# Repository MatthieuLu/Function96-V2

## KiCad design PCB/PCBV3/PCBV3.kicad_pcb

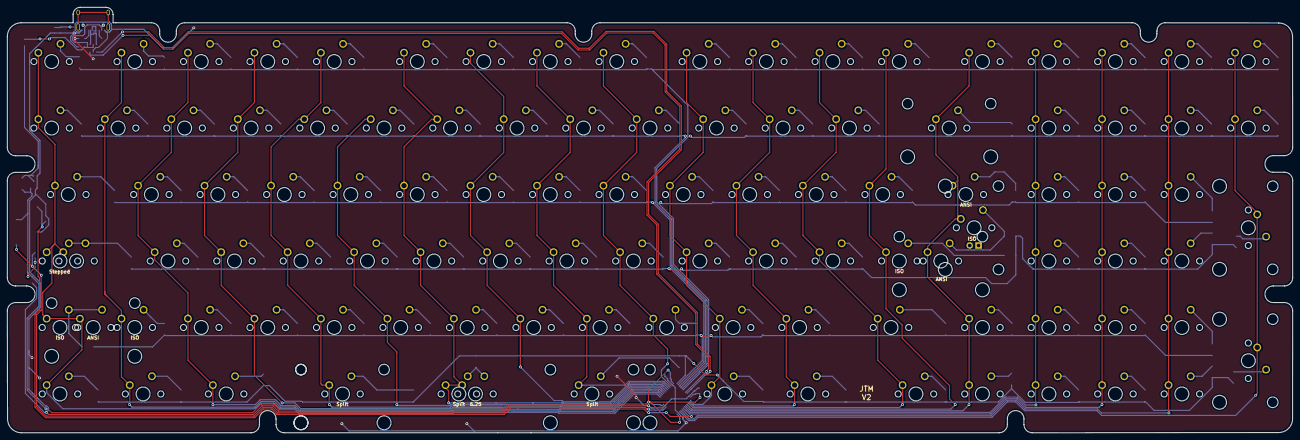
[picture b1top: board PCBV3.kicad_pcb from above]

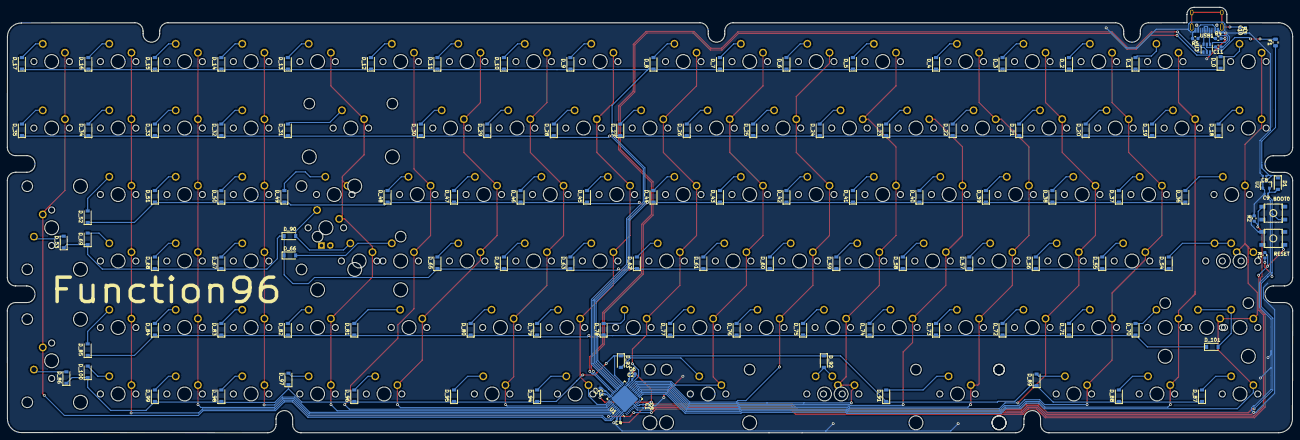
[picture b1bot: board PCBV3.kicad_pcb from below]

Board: 2 copper layers, 368.3 x 121.9 mm, 232 parts (126 on the bottom side), 140 nets.

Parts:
BOOT0: SW_PUSH; SKQG-1155865
C1: 10nF; C_0402_1005Metric
C2, C3, C4: 100nF; C_0402_1005Metric
C5: 1uF; C_0402_1005Metric
C6, C7: 4.7uF; C_0603_1608Metric
C8, C9: 0.1uF; C_0402_1005Metric
C10: 4.7nF; C_0603_1608Metric
C11: 100nF; C_0603_1608Metric
D1: D_Schottky; D_SOD-123
D_0, D_1, D_2, D_3, D_4, D_5, D_6, D_7, D_8, D_9, D_10, D_11, D_12, D_13, D_14, D_15, D_16, D_17, D_18, D_19, D_20, D_21, D_22, D_23, D_24, D_25, D_26, D_27, D_28, D_29, D_30, D_31, D_32, D_33, D_34, D_35, D_36, D_37, D_38, D_39, D_40, D_41, D_42, D_43, D_44, D_45, D_46, D_47, D_48, D_49, D_50, D_51, D_52, D_53, D_54, D_55, D_56, D_57, D_58, D_59, D_60, D_61, D_62, D_63, D_64, D_65, D_66, D_67, D_68, D_69, D_70, D_71, D_72, D_73, D_74, D_75, D_76, D_77, D_78, D_79, D_80, D_81, D_82, D_83, D_84, D_85, D_86, D_87, D_88, D_89, D_90, D_91, D_92, D_93, D_94, D_95, D_96, D_97, D_98, D_99, D_100, D_101: D; D_SOD-123
F1: Polyfuse_Small; Fuse_0805_2012Metric
K_0, K_1, K_2, K_3, K_4, K_5, K_6, K_7, K_8, K_9, K_10, K_11, K_12, K_13, K_14, K_15, K_16, K_17, K_18, K_19, K_20, K_21, K_22, K_23, K_24, K_25, K_26, K_27, K_28, K_29, K_30, K_32, K_33, K_34, K_35, K_37, K_38, K_39, K_40, K_41, K_42, K_43, K_44, K_45, K_46, K_47, K_48, K_50, K_51, K_52, K_55, K_56, K_57, K_58, K_59, K_60, K_61, K_62, K_63, K_64, K_65, K_67, K_68, K_69, K_71, K_72, K_73, K_74, K_75, K_76, K_77, K_78, K_79, K_80, K_82, K_83, K_84, K_85, K_96, K_97, K_98, K_99, K_100: KEYSW; MXOnly-1U-NoLED
K_31, K_53, K_86: KEYSW; MXOnly-2U-NoLED
K_36, K_49ANSISlash1: KEYSW; MXOnly-1.5U-NoLED
K_54, K_81: KEYSW; MXOnly-1.75U-NoLED
K_87, K_88, K_89, K_92, K_94, K_95, K_101: KEYSW; MXOnly-1.25U-NoLED
K_90: KEYSW; MXOnly-6.25U-NoLED
K_91: KEYSW; MXOnly-2.25U-NoLED
K_93: KEYSW; MXOnly-2.75U-NoLED
K_ANSIEnter1: KEYSW; MXOnly-2.25U-NoLED
K_ANSIShift1: KEYSW; MXOnly-2.25U-NoLED
K_ISO1u1R1, K_ISO1uL1: KEYSW; MXOnly-1U-NoLED
K_ISOEnter1: KEYSW; MXOnly-ISO-ReversedStabilizers
K_ISOShift1: KEYSW; MXOnly-1.25U-NoLED
R1, R2: 10k; R_0603_1608Metric
R3: 1M; R_0603_1608Metric
R4, R5: 5.1k; R_0603_1608Metric
RESET: SW_PUSH; SKQG-1155865
U1: STM32F072CBUx; QFN-48-1EP_7x7mm_P0.5mm_EP5.6x5.6mm
U2: MCP1700-3302E_SOT23; SOT-23
U3: USBLC6-2SC6; SOT-23-6
USB1: HRO-TYPE-C-31-M-12

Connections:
+3V3: BOOT0.2, C1.1, C2.1, C3.1, C4.1, C5.1, C6.1, C7.1, C9.1, D1.2, R1.1, U1.9, U1.24, U1.36, U1.48, U2.2
+5V: C8.1, D1.1, F1.1, U2.3
BOOT0: BOOT0.1, R2.1, U1.44
D+: U1.33, U3.1
D-: U1.32, U3.3
DBus+: U3.6, USB1.6, USB1.8
DBus-: U3.4, USB1.5, USB1.7
GND: C1.2, C2.2, C3.2, C4.2, C5.2, C6.2, C7.2, C8.2, C9.2, C10.1, C11.1, R2.2, R3.2, R4.2, R5.2, RESET.2, U1.8, U1.23, U1.35, U1.47, U1.49, U2.1, U3.2, USB1.1, USB1.12
NRST: R1.2, RESET.1, U1.7
unnamed: C10.2, R3.1, USB1.13
unnamed: D_0.2, K_0.2
unnamed: D_1.2, K_1.2
unnamed: D_2.2, K_2.2
unnamed: D_3.2, K_3.2
unnamed: D_4.2, K_4.2
unnamed: D_5.2, K_5.2
unnamed: D_6.2, K_6.2
unnamed: D_7.2, K_7.2
unnamed: D_8.2, K_8.2
unnamed: D_9.2, K_9.2
unnamed: D_10.2, K_10.2
unnamed: D_11.2, K_11.2
unnamed: D_12.2, K_12.2
unnamed: D_13.2, K_13.2
unnamed: D_14.2, K_14.2
unnamed: D_15.2, K_15.2
unnamed: D_16.2, K_16.2
unnamed: D_17.2, K_17.2
unnamed: D_18.2, K_18.2
unnamed: D_19.2, K_19.2
unnamed: D_20.2, K_20.2
unnamed: D_21.2, K_21.2
unnamed: D_22.2, K_22.2
unnamed: D_23.2, K_23.2
unnamed: D_24.2, K_24.2
unnamed: D_25.2, K_25.2
unnamed: D_26.2, K_26.2
unnamed: D_27.2, K_27.2
unnamed: D_28.2, K_28.2
unnamed: D_29.2, K_29.2
unnamed: D_30.2, K_30.2
unnamed: D_31.2, K_31.2
unnamed: D_32.2, K_32.2
unnamed: D_33.2, K_33.2
unnamed: D_34.2, K_34.2
unnamed: D_35.2, K_35.2
unnamed: D_36.2, K_36.2
unnamed: D_37.2, K_37.2
unnamed: D_38.2, K_38.2
unnamed: D_39.2, K_39.2
unnamed: D_40.2, K_40.2
unnamed: D_41.2, K_41.2
unnamed: D_42.2, K_42.2
unnamed: D_43.2, K_43.2
unnamed: D_44.2, K_44.2
unnamed: D_45.2, K_45.2
unnamed: D_46.2, K_46.2
unnamed: D_47.2, K_47.2
unnamed: D_48.2, K_48.2
unnamed: D_49.2, K_49ANSISlash1.2
unnamed: D_50.2, K_50.2
unnamed: D_51.2, K_51.2
unnamed: D_52.2, K_52.2
unnamed: D_53.2, K_53.2
unnamed: D_54.2, K_54.2, K_101.2
unnamed: D_55.2, K_55.2
unnamed: D_56.2, K_56.2
unnamed: D_57.2, K_57.2
unnamed: D_58.2, K_58.2
unnamed: D_59.2, K_59.2
unnamed: D_60.2, K_60.2
unnamed: D_61.2, K_61.2
unnamed: D_62.2, K_62.2
unnamed: D_63.2, K_63.2
unnamed: D_64.2, K_64.2
unnamed: D_65.2, K_65.2
unnamed: D_66.2, K_ISO1u1R1.2
unnamed: D_67.2, K_67.2
unnamed: D_68.2, K_68.2
unnamed: D_69.2, K_69.2
unnamed: D_70.2, K_ISO1uL1.2
unnamed: D_71.2, K_71.2
unnamed: D_72.2, K_72.2
unnamed: D_73.2, K_73.2
unnamed: D_74.2, K_74.2
unnamed: D_75.2, K_75.2
unnamed: D_76.2, K_76.2
unnamed: D_77.2, K_77.2
unnamed: D_78.2, K_78.2
unnamed: D_79.2, K_79.2
unnamed: D_80.2, K_80.2
unnamed: D_81.2, K_81.2
unnamed: D_82.2, K_82.2
unnamed: D_83.2, K_83.2
unnamed: D_84.2, K_84.2
unnamed: D_85.2, K_85.2
unnamed: D_86.2, K_86.2
unnamed: D_87.2, K_87.2
unnamed: D_88.2, K_88.2
unnamed: D_89.2, K_89.2
unnamed: D_90.2, K_ANSIEnter1.2, K_ISOEnter1.2
unnamed: D_91.2, K_91.2
unnamed: D_92.2, K_90.2, K_92.2
unnamed: D_93.2, K_93.2
unnamed: D_94.2, K_94.2
unnamed: D_95.2, K_95.2
unnamed: D_96.2, K_96.2
unnamed: D_97.2, K_97.2
unnamed: D_98.2, K_98.2
unnamed: D_99.2, K_99.2
unnamed: D_100.2, K_100.2
unnamed: D_101.2, K_ANSIShift1.2, K_ISOShift1.2
unnamed: R4.1, USB1.4
unnamed: R5.1, USB1.10
VBUS: C11.2, F1.2, U3.5, USB1.2, USB1.11
col0: K_0.1, K_18.1, K_36.1, K_54.1, K_87.1, K_101.1, K_ANSIShift1.1, K_ISOShift1.1, U1.13
col1: K_1.1, K_19.1, K_88.1, K_ISO1uL1.1, U1.14
col2: K_2.1, K_20.1, K_37.1, K_55.1, K_71.1, K_89.1, U1.15
col3: K_3.1, K_21.1, K_38.1, K_56.1, K_72.1, U1.16
col4: K_4.1, K_22.1, K_39.1, K_57.1, K_73.1, K_91.1, U1.17
col5: K_23.1, K_40.1, K_58.1, K_74.1, U1.18
col6: K_5.1, K_24.1, K_41.1, K_59.1, K_75.1, K_90.1, K_92.1, U1.19
col7: K_6.1, K_25.1, K_42.1, K_60.1, K_76.1, U1.20
col8: K_7.1, K_26.1, K_43.1, K_61.1, K_77.1, K_93.1, U1.21
col9: K_8.1, K_27.1, K_44.1, K_62.1, K_78.1, U1.22
col10: K_9.1, K_28.1, K_45.1, K_63.1, K_79.1, K_94.1, U1.37
col11: K_10.1, K_29.1, K_46.1, K_64.1, K_80.1, K_95.1, U1.38
col12: K_11.1, K_30.1, K_47.1, K_65.1, K_81.1, K_96.1, U1.39
col13: K_12.1, K_48.1, K_ISO1u1R1.1, U1.40
col14: K_13.1, K_31.1, K_49ANSISlash1.1, K_82.1, K_97.1, K_ANSIEnter1.1, K_ISOEnter1.1, U1.41
col15: K_14.1, K_32.1, K_50.1, K_67.1, K_83.1, K_98.1, U1.42
col16: K_15.1, K_33.1, K_51.1, K_68.1, K_84.1, K_99.1, U1.43
col17: K_16.1, K_34.1, K_52.1, K_69.1, K_85.1, K_100.1, U1.45
col18: K_17.1, K_35.1, K_53.1, K_86.1, U1.46
row0: D_0.1, D_1.1, D_2.1, D_3.1, D_4.1, D_5.1, D_6.1, D_7.1, D_8.1, D_9.1, D_10.1, D_11.1, D_12.1, D_13.1, D_14.1, D_15.1, D_16.1, D_17.1, U1.30
row1: D_18.1, D_19.1, D_20.1, D_21.1, D_22.1, D_23.1, D_24.1, D_25.1, D_26.1, D_27.1, D_28.1, D_29.1, D_30.1, D_31.1, D_32.1, D_33.1, D_34.1, D_35.1, U1.29
row2: D_36.1, D_37.1, D_38.1, D_39.1, D_40.1, D_41.1, D_42.1, D_43.1, D_44.1, D_45.1, D_46.1, D_47.1, D_48.1, D_49.1, D_50.1, D_51.1, D_52.1, U1.28
row3: D_53.1, D_54.1, D_55.1, D_56.1, D_57.1, D_58.1, D_59.1, D_60.1, D_61.1, D_62.1, D_63.1, D_64.1, D_65.1, D_66.1, D_67.1, D_68.1, D_69.1, D_90.1, U1.27
row4: D_70.1, D_71.1, D_72.1, D_73.1, D_74.1, D_75.1, D_76.1, D_77.1, D_78.1, D_79.1, D_80.1, D_81.1, D_82.1, D_83.1, D_84.1, D_85.1, D_101.1, U1.26
row5: D_86.1, D_87.1, D_88.1, D_89.1, D_91.1, D_92.1, D_93.1, D_94.1, D_95.1, D_96.1, D_97.1, D_98.1, D_99.1, D_100.1, U1.25

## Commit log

2020-08-18 PCB created
2020-08-18 Top Plate Started
    Still need to add cutouts for Plate and get dimensions for F-Row blockers
2020-08-19 V2 CAD finished.
2020-08-20 Updates to PCB
    Moved Numpad + and Enter diodes.
2020-08-20 Updates to CAD
2020-08-20 Updated some CAD
2020-08-20 Added ESD Protection to PCB
2020-08-21 Aesthetic Keyboard Updates
2020-08-21 Aesthetic changes
2020-08-23 Updates to design
2020-08-24 Updates to CAD to address acoustics concerns.
2020-08-25 Updates to Plate CAD
2020-09-09 CAD Updates
2020-09-14 Updated to SW 2020
2020-09-19 Updated so that USB-C is on the bottom of the PCB again
2020-09-20 Made V2 Screwless Exterior
2020-09-21 Updates to CAD for caseless design and PCB
2020-09-23 Minor Updates
2020-10-21 Various Updates
2020-11-18 BIG CHANGES
2020-11-18 big change
